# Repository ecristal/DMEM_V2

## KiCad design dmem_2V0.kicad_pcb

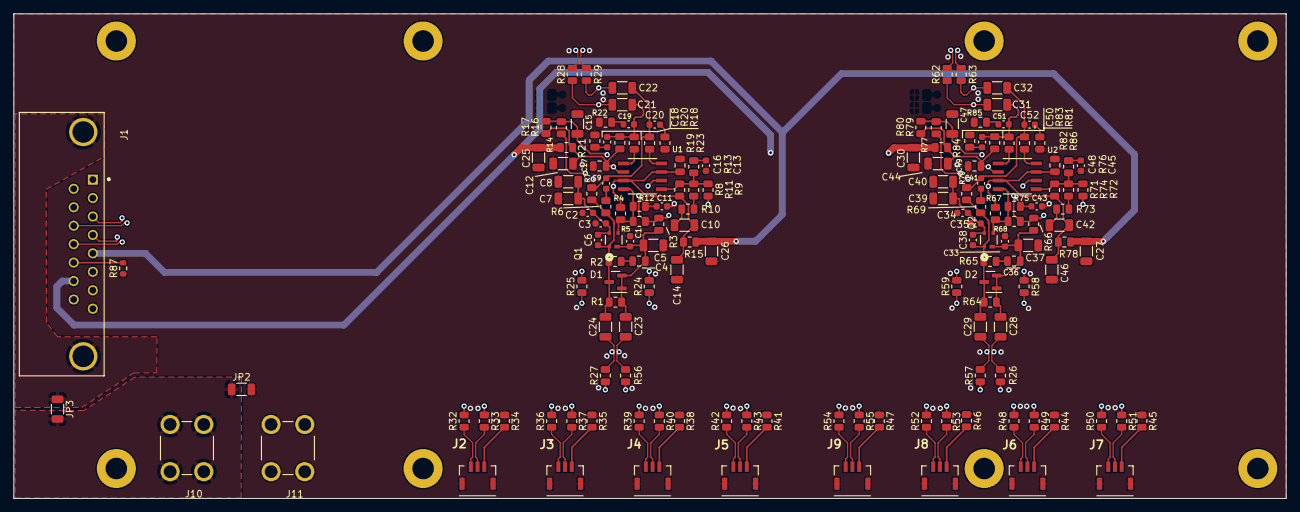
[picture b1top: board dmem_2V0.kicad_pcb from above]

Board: 4 copper layers, 189.0 x 72.0 mm, 154 parts (0 on the bottom side), 86 nets.

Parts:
C1, C2, C3, C11, C13, C33, C34, C35, C43, C45: 1n; C_0603_1608Metric
C4, C36: 3n; C_0805_2012Metric
C5, C7, C8, C10, C12, C14, C15, C21, C22, C23, C24, C28, C29, C31, C32, C37, C39, C40, C42, C44, C46, C47: 100n; C_1206_3216Metric
C6, C38: 10p; C_0603_1608Metric
C9, C18, C41, C50: 68p; C_0603_1608Metric
C16, C17, C48, C49: 10n; C_0805_2012Metric
C19, C20, C51, C52: 470p; C_0603_1608Metric
C25, C26, C27, C30: 47u; C_1206_3216Metric
D1, D2: SB01-15C; SOT-23
J1: D15P33E4GV00LF; AMPHENOL_D15P33E4GV00LF
J2, J3, J4, J5, J6, J7, J8, J9: T1M-03-F-SV-L; T1M03FSVL
J10, J11: 7701-3; KEYSTONE_7701-3
JP2, JP3: Jumper_2_Open; R_1206_3216Metric
Q1, Q2: BFP640; BFP640ESDH6327XTSA1
R1, R64: 20k; R_0805_2012Metric
R2, R65: 3; R_0805_2012Metric
R3, R14, R15, R66, R77, R78: 4R7; R_0805_2012Metric
R4, R67: 4k7; R_0805_2012Metric
R5, R9, R68, R72: 15k; R_0805_2012Metric
R6, R21, R69, R84: 68; R_0805_2012Metric
R7, R70: 13K; R_0805_2012Metric
R8, R71: 30k; R_0805_2012Metric
R10, R73: 475; R_0805_2012Metric
R11, R74: 5k1; R_0805_2012Metric
R12, R13, R75, R76: 680; R_0805_2012Metric
R16, R17, R79, R80: R; R_0805_2012Metric
R18, R19, R22, R23, R28, R29, R62, R63, R81, R82, R85, R86: 49R9; R_0805_2012Metric
R20, R83: 33K; R_0805_2012Metric
R24, R25, R58, R59: 1K2; R_0805_2012Metric
R26, R27, R34, R35, R38, R41, R44, R45, R46, R47, R56, R57: 0; R_0805_2012Metric
R32, R33, R36, R37, R39, R40, R42, R43, R48, R49, R50, R51, R52, R53, R54, R55: 1; R_0805_2012Metric
R87: 0; R_0603_1608Metric
U1, U2: THS4531AID

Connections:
/+CE: C26.2, C27.2, J1.5, R15.1, R78.1
/+CE_R: C25.2, C30.2, J1.14, R14.1, R77.1
/cold_amplifier_ch1/cold amplifier/inn: C1.1, C2.1, C3.1, C4.2, C5.1, C6.2, C7.1, C8.1, C23.2, D1.1 (A), D1.2 (A), Q1.2, R1.2, R3.1
/cold_amplifier_ch1/cold amplifier/inp: C6.1, C24.2, D1.3 (K), Q1.1, R1.1, R2.1, R6.1, R7.1
/cold_amplifier_ch1/cold amplifier/outn: C9.2, C20.1, C22.1, R7.2, R19.2
/cold_amplifier_ch1/cold amplifier/outp: C18.1, C19.1, C21.1, R18.2, R20.1
/cold_amplifier_ch1/input+: C24.1, R25.1, R27.2
/cold_amplifier_ch1/input-: C23.1, R24.1, R56.2
/cold_amplifier_ch1/output+: C21.2, R24.2, R28.1
/cold_amplifier_ch1/output-: C22.2, R25.2, R29.1
/cold_amplifier_ch1/sipmA+: J2.3, R32.1
/cold_amplifier_ch1/sipmA-: J2.2, R33.2
/cold_amplifier_ch1/sipmB+: J3.3, R36.1
/cold_amplifier_ch1/sipmB-: J3.2, R37.2
/cold_amplifier_ch1/sipmC+: J4.3, R39.1
/cold_amplifier_ch1/sipmC-: J4.2, R40.2
/cold_amplifier_ch1/sipmD+: J5.3, R42.1
/cold_amplifier_ch1/sipmD-: J5.2, R43.2
/cold_amplifier_ch2/cold amplifier/inn: C28.2, C33.1, C34.1, C35.1, C36.2, C37.1, C38.2, C39.1, C40.1, D2.1 (A), D2.2 (A), Q2.2, R64.2, R66.1
/cold_amplifier_ch2/cold amplifier/inp: C29.2, C38.1, D2.3 (K), Q2.1, R64.1, R65.1, R69.1, R70.1
/cold_amplifier_ch2/cold amplifier/outn: C32.1, C41.2, C52.1, R70.2, R82.2
/cold_amplifier_ch2/cold amplifier/outp: C31.1, C50.1, C51.1, R81.2, R83.1
/cold_amplifier_ch2/input+: C29.1, R57.2, R59.1
/cold_amplifier_ch2/input-: C28.1, R26.2, R58.1
/cold_amplifier_ch2/output+: C31.2, R58.2, R62.1
/cold_amplifier_ch2/output-: C32.2, R59.2, R63.1
/cold_amplifier_ch2/sipmA+: J9.3, R54.1
/cold_amplifier_ch2/sipmA-: J9.2, R55.2
/cold_amplifier_ch2/sipmB+: J8.3, R52.1
/cold_amplifier_ch2/sipmB-: J8.2, R53.2
/cold_amplifier_ch2/sipmC+: J6.3, R48.1
/cold_amplifier_ch2/sipmC-: J6.2, R49.2
/cold_amplifier_ch2/sipmD+: J7.3, R50.1
/cold_amplifier_ch2/sipmD-: J7.2, R51.2
/out1+: J1.12, R28.2
/out1-: J1.4, R29.2
/out2+: J1.11, R62.2
/out2-: J1.3, R63.2
GND: C1.2, C2.2, C3.2, C5.2, C7.2, C8.2, C11.2, C12.2, C13.2, C14.2, C15.2, C16.2, C17.2, C25.1, C26.1, C27.1, C30.1, C33.2, C34.2, C35.2, C37.2, C39.2, C40.2, C43.2, C44.2, C45.2, C46.2, C47.2, C48.2, C49.2, J1.6, J1.7, J1.8, J1.15, J2.MP1, J2.MP2, J3.MP1, J3.MP2, J4.MP1, J4.MP2, J5.MP1, J5.MP2, J6.MP1, J6.MP2, J7.MP1, J7.MP2, J8.MP1, J8.MP2, J9.MP1, J9.MP2, J11.1_1 (1), J11.1_2 (1__1), J11.1_3 (1__2), J11.1_4 (1__3), JP2.2 (B), R21.2, R22.2, R23.2, R34.1, R35.1, R38.1, R41.1, R44.1, R45.1, R46.1, R47.1, R84.2, R85.2, R86.2, R87.1
unnamed: C4.1, R2.2
unnamed: C9.1, R6.2
unnamed: C10.2, R10.1
unnamed: C11.1, R12.2
unnamed: C13.1, R13.2
unnamed: C18.2, R21.1
unnamed: C19.2, R22.1
unnamed: C20.2, R23.1
unnamed: C36.1, R65.2
unnamed: C41.1, R69.2
unnamed: C42.2, R73.1
unnamed: C43.1, R75.2
unnamed: C45.1, R76.2
unnamed: C50.2, R84.1
unnamed: C51.2, R85.1
unnamed: C52.2, R86.1
unnamed: J1.13, R87.2
unnamed: J2.1, R34.2
unnamed: J3.1, R35.2
unnamed: J4.1, R38.2
unnamed: J5.1, R41.2
unnamed: J6.1, R44.2
unnamed: J7.1, R45.2
unnamed: J8.1, R46.2
unnamed: J9.1, R47.2
unnamed: J10.1_1 (1), J10.1_2 (1__1), J10.1_3 (1__2), J10.1_4 (1__3), JP2.1 (A), JP3.2 (B)
unnamed: J1.16, JP3.1 (A)
unnamed: Q1.3, R4.2, R5.1, R12.1, U1.8 (+)
unnamed: Q2.3, R67.2, R68.1, R75.1, U2.8 (+)
unnamed: R10.2, R11.1
unnamed: R8.2, R9.1, R11.2, R13.1, U1.1 (-)
unnamed: R18.1, U1.5 (-)
unnamed: R19.1, U1.4 (+)
unnamed: R26.1, R48.2, R50.2, R52.2, R54.2
unnamed: R27.1, R33.1, R37.1, R40.1, R43.1
unnamed: R32.2, R36.2, R39.2, R42.2, R56.1
unnamed: R49.1, R51.1, R53.1, R55.1, R57.1
unnamed: R71.2, R72.1, R74.2, R76.1, U2.1 (-)
unnamed: R73.2, R74.1
unnamed: R81.1, U2.5 (-)
unnamed: R82.1, U2.4 (+)
unnamed: C10.1, C14.1, C16.1, R4.1, R8.1, R15.2, R16.1, U1.3 (Vs+), U1.7 (*PD)
unnamed: C15.1, R16.2, R17.1, U1.2 (Vocm)
unnamed: C12.1, C17.1, R3.2, R5.2, R9.2, R14.2, R17.2, R20.2, U1.6 (Vs-)
unnamed: C42.1, C46.1, C48.1, R67.1, R71.1, R78.2, R79.1, U2.3 (Vs+), U2.7 (*PD)
unnamed: C47.1, R79.2, R80.1, U2.2 (Vocm)
unnamed: C44.1, C49.1, R66.2, R68.2, R72.2, R77.2, R80.2, R83.2, U2.6 (Vs-)

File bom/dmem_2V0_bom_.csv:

Component,References,Value,Quantity Per PCB,Part Number,Manufacturer,Digikey Part Number,Description
1,C6 C38,10p,2,GCM1885C1H100JA16D,Murata Electronics,490-4766-1-ND,"10 pF ±5% 50V Ceramic Capacitor C0G, NP0 0603 (1608 Metric)"
2,C9 C18 C41 C50,68p,4,CL10C680JB8NNNC,Samsung Electro-Mechanics,1276-1135-1-ND,"68 pF ±5% 50V Ceramic Capacitor C0G, NP0 0603 (1608 Metric)"
3,C19 C20 C51 C52,470p,4,CL10C471JB8NNNC,Samsung Electro-Mechanics,1276-1168-1-ND,"470 pF ±5% 50V Ceramic Capacitor C0G, NP0 0603 (1608 Metric)"
4,C1 C3 C11 C13 C33 C35 C43 C45,1n,8,GRM1885C1H102JA01D,Murata Electronics,490-1451-1-ND,"1000 pF ±5% 50V Ceramic Capacitor C0G, NP0 0603 (1608 Metric)"
5,C4 C36,3n,2,GCM1885C1H302FA16J,Murata Electronics,490-GCM1885C1H302FA16JCT-ND,"3000 pF ±1% 50V Ceramic Capacitor C0G, NP0 0603 (1608 Metric)"
6,C16 C17 C48 C49,10n,4,GRM1885C1H103JA01D,Murata Electronics,490-9666-1-ND,"10000 pF ±5% 50V Ceramic Capacitor C0G, NP0 0603 (1608 Metric)"
7,C5 C7 C10 C12 C14 C15 C37 C39 C42 C44 C46 C47,100n,12,GRM31C5C1H104JA01L,Murata Electronics,490-6505-1-ND,"0.1 µF ±5% 50V Ceramic Capacitor C0G, NP0 1206 (3216 Metric)"
8,C21 C22 C23 C24 C28 C29 C31 C32,100n,8,GRM3195C2A104JA01D,Murata Electronics,490-GRM3195C2A104JA01DCT-ND,"0.1 µF ±5% 100V Ceramic Capacitor C0G, NP0 1206 (3216 Metric)"
9,C25 C26 C27 C30,22u,4,GRM31C5C1H224JE02L,Murata Electronics,490-GRM31C5C1H224JE02LCT-ND,"0.22 µF ±5% 50V Ceramic Capacitor C0G, NP0 1206 (3216 Metric)"
10,D1 D2,BAR46FILM,2,BAR46FILM,STMicroelectronics,497-12128-1-ND,Diode 100 V 150mA Surface Mount SOT-23
11,J10 J11,7701-3,2,7701-3,Keystone Electronics,36-7701-3-ND,"4 Pin Screw Terminal, Power Tap 6-32 Through Hole"
12,J1,D15P33E4GV00LF,1,D15P33E4GV00LF,Amphenol ICC (FCI),609-1492-ND,"15 Position D-Sub Plug, Male Pins Connector"
13,J12,D15S33E4GV00LF,1,D15S33E4GV00LF,Amphenol ICC (FCI),609-1498-ND,"15 Position D-Sub Receptacle, Female Sockets Connector"
14,J2 J3 J4 J5 J6 J7 J8 J9,T1M-03-F-SV-L,8,T1M-03-F-SV-L,SAMTEC,SAM15301CT-ND,"Connector Header Surface Mount 3 position 0.039"" (1.00mm)"
15,JP1 JP2 JP3,Jumper_2_Open,3,RMCF1206ZT0R00,Stackpole Electronics Inc,RMCF1206ZT0R00CT-ND,0 Ohms Jumper Chip Resistor 1206 (3216 Metric) Automotive AEC-Q200 Thick Film
16,Q1 Q2,BFP640,2,BFP640ESDH6327XTSA1,Infineon Technologies,BFP640ESDH6327XTSA1CT-ND,RF Transistor NPN 4.7V 50mA 46GHz 200mW Surface Mount PG-SOT343-4-2
17,R26 R27 R30 R31 R34 R35 R38 R41 R44 R45 R46 R47 R56 R57 R60 R61 R87 R88 R89 R90 R91 R92,0,22,MCU0805MZ0000ZP500,Vishay Beyschlag/Draloric/BC Components,749-MCU0805MZ0000ZP500CT-ND,"0 Ohms Jumper Chip Resistor 0805 (2012 Metric) Anti-Sulfur, Automotive AEC-Q200 Thin Film"
18,R32 R33 R36 R37 R39 R40 R42 R43 R48 R49 R50 R51 R52 R53 R54 R55,1,16,RT0805BRD071RL,YAGEO,13-RT0805BRD071RLCT-ND,"1 Ohms ±0.1% 0.125W, 1/8W Chip Resistor 0805 (2012 Metric) Thin Film"
19,R2 R65,3,2,RT0805DRD073RL,YAGEO,YAG5007CT-ND,"3 Ohms ±0.5% 0.125W, 1/8W Chip Resistor 0805 (2012 Metric) Thin Film"
20,R3 R14 R15 R66 R77 R78,4R7,6,RNCP0805FTD4R70,Stackpole Electronics Inc,RNCP0805FTD4R70CT-ND,"4.7 Ohms ±1% 0.25W, 1/4W Chip Resistor 0805 (2012 Metric) Anti-Sulfur Thin Film"
21,R18 R19 R22 R23 R28 R29 R62 R63 R81 R82 R85 R86,49R9,12,ERA-6AEB49R9V,Panasonic Electronic Components,P49.9DACT-ND,"49.9 Ohms ±0.1% 0.125W, 1/8W Chip Resistor 0805 (2012 Metric) Automotive AEC-Q200 Thin Film"
22,R6 R21 R69 R84,68,4,ERA-6AEB680V,Panasonic Electronic Components,P68DACT-ND,"68 Ohms ±0.1% 0.125W, 1/8W Chip Resistor 0805 (2012 Metric) Automotive AEC-Q200 Thin Film"
23,R10 R73,475,2,ERA-6AEB4750V,Panasonic Electronic Components,P475DACT-ND,"475 Ohms ±0.1% 0.125W, 1/8W Chip Resistor 0805 (2012 Metric) Automotive AEC-Q200 Thin Film"
24,R12 R13 R75 R76,680,4,ERA-6AEB681V,Panasonic Electronic Components,P680DACT-ND,"680 Ohms ±0.1% 0.125W, 1/8W Chip Resistor 0805 (2012 Metric) Automotive AEC-Q200 Thin Film"
25,R24 R25 R58 R59,1K2,4,ERA-6AEB122V,Panasonic Electronic Components,P1.2KDACT-ND,"1.2 kOhms ±0.1% 0.125W, 1/8W Chip Resistor 0805 (2012 Metric) Automotive AEC-Q200 Thin Film"
26,R4 R67,4K7,2,ERA-6AEB472V,Panasonic Electronic Components,P4.7KDACT-ND,"4.7 kOhms ±0.1% 0.125W, 1/8W Chip Resistor 0805 (2012 Metric) Automotive AEC-Q200 Thin Film"
27,R11 R74,5K1,2,ERA-6AEB512V,Panasonic Electronic Components,P5.1KDACT-ND,"5.1 kOhms ±0.1% 0.125W, 1/8W Chip Resistor 0805 (2012 Metric) Automotive AEC-Q200 Thin Film"
28,R7 R70,13K,2,ERA-6AEB133V,Panasonic Electronic Components,P13KDACT-ND,"13 kOhms ±0.1% 0.125W, 1/8W Chip Resistor 0805 (2012 Metric) Automotive AEC-Q200 Thin Film"
29,R5 R9 R68 R72,15K,4,RT0805BRD0715KL,YAGEO,YAG1787CT-ND,"15 kOhms ±0.1% 0.125W, 1/8W Chip Resistor 0805 (2012 Metric) Thin Film"
30,R1 R64,20K,2,ERA-6AEB203V,Panasonic Electronic Components,P20KDACT-ND,"20 kOhms ±0.1% 0.125W, 1/8W Chip Resistor 0805 (2012 Metric) Automotive AEC-Q200 Thin Film"
31,R8 R71,30K,2,ERA-6AEB303V,Panasonic Electronic Components,P30KDACT-ND,"30 kOhms ±0.1% 0.125W, 1/8W Chip Resistor 0805 (2012 Metric) Automotive AEC-Q200 Thin Film"
32,R20 R83,33K,2,ERA-6AEB333V,Panasonic Electronic Components,P33KDACT-ND,"33 kOhms ±0.1% 0.125W, 1/8W Chip Resistor 0805 (2012 Metric) Automotive AEC-Q200 Thin Film"
33,R16 R17 R79 R80,R,4,,,,DNP
34,U1 U2,THS4531AID,2,THS4531AID,Texas Instruments,296-35604-5-ND,"Differential Amplifier 1 Circuit Differential, Rail-to-Rail 8-SOIC"





Component Groups:,34
Component Count:,161
Fitted Components:,161
Number of PCBs:,1
Total components:,161
Schematic Version:,
Schematic Date:,
PCB Variant:,default
BoM Date:,12/13/2024 2:41:06 PM
Schematic Source:,dmem_2V0.kicad_sch
KiCad Version:,Eeschema 7.0.7

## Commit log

2024-12-11 first commit: adding git ignore
2024-12-11 Adding KiCad project files
2024-12-11 Changed R25,R24,R59,R58 values from 1K5 to 1K2.
2024-12-11 Removed R30, R31 and mirrors
2024-12-11 Changed solid plane pattern to crosshatch pattern; increased plane margin to 0.5 and minimun width to 0.5; thermal relief spacing to 0.5 and width of the thermal relief to 0.7
2024-12-11 Removed one pair of 1nF and 100nF capacitors connected to pin 2 of the BFP640 to allow the 100nF to be closer to the pin
2024-12-11 Added jumpers to connect ground to mounting holes to ground
2024-12-11 Added DVDM constraints and layer stack up
2024-12-12 DMEM combination
2024-12-12 vias stiching planes
2024-12-13 Moved connectors SiPM flex connectorsto both sides; rectangular vias stitching pattern
2024-12-13 completed BOM list; replaced 47u with 33u capacitor
2024-12-13 added logos and board info in silkscreen
2024-12-13 Adding test points and arrows to DB15s
2024-12-16 Changed footprint to removed unused silkscreen symbols; silkscreen more legible; changed texts next to arrows; changed wrong 0.22u cap to 47u
2024-12-16 gerber & drill generation; added placement folder and step file folder
2024-12-16 added bom files
2024-12-16 Added netlist file
2024-12-18 Solved error in netlist; input connector was in a mirror configuration; solved also DB15 error in netlist
2026-04-01 Version tested at coldbox March 2026
